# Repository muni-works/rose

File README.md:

# rose

rose is Muni's humanoid robot line: three sizes (mini, full, mega) meant to share
one structure and one electronics stack. The name is the past tense of *rise*.

**State today: design stage.** This repository is CAD sources, sizing and checking
scripts, fabrication packages, PCB designs and renders. It records no built robot:
the fab packages say nothing has been ordered or cut
([`body/fab/README.md`](body/fab/README.md), [`arm/V10.8.md`](arm/V10.8.md)),
and every image here is a render
([`head/renders/release/README.md`](head/renders/release/README.md)).
Numbers are model outputs or vendor figures, not measurements, unless a file says
otherwise. Muni's overall plan, and where rose sits in it, is at
<https://muni.works/research>.

| | |
|---|---|
|  |  |
| rose mini with the cortex head (render) | rose full, same design language (render) |

## Layout

| path | what it is |
|---|---|
| [`body/`](body) | The humanoid: mini (100 cm, 22 DoF, router-cut 3.2 mm plate, printed skins) and full, generated from one set of Python sources. Its fab package is in [`body/fab/`](body/fab). |
| [`head/`](head) | cortex, the head: a detachable module with the compute, battery, cameras, mics and a screen face, which docks on the neck or sits on a desk. Spec in [`SPEC.md`](head/SPEC.md); the "node" redesign, locked at v1.21 for a first print, in [`NODE-BRIEF.md`](head/NODE-BRIEF.md). |
| [`arm/`](arm) | lymb, a RobStride table arm that is also rose's arm. Current revision v10.8 ([`V10.8.md`](arm/V10.8.md)); v9 is kept bit-identical with a complete fab package. |
| [`electronics/`](electronics) | The boards: [`brain/`](electronics/brain) (RK3588S2 + STM32H7 compute), [`limb-controller/`](electronics/limb-controller) (one per limb), and [`brand/`](electronics/brand) (logo footprints for board art). |
| [`sizing/`](sizing) | The size ladder ([`family.py`](sizing/family.py)) and the mega actuator sizing ([`MEGA-SIZING.md`](sizing/MEGA-SIZING.md)). |

Each folder has a README with its run commands. Earlier design passes (the first
950 mm mini, the MyActuator full at 1800 mm, the rose-1 mega study, the quadruped
leg the body grew out of, the first box arm, the head mockups) were removed in
November 2026. They are in history at the tag
[`pre-restructure`](https://github.com/muni-works/rose/tree/pre-restructure).

## Tools

Sources are Python generators and [loon](https://vcad.io) files.

- **Python 3** for every sizing and checking script. `body/` also needs
  `numpy trimesh manifold3d shapely ezdxf scikit-image` (plus `rectpack` for
  `fab/make.py`).
- **[vcad](https://github.com/muni-works/vcad)** to evaluate and render `.loon`
  (`vcad`, `vcad-render`).
- **KiCad** (`kicad-cli`) for the board flows.

A few scripts read sibling checkouts under `~/Developer` (for example the Booster
K1 reference meshes in `body/k1.py`). `*.step` files are in Git LFS.

```bash
python3 sizing/family.py                       # the size ladder

cd body
python3 fab/make.py                            # plates (DXF), shells (STL), glass
python3 rom_mini.py                            # range of motion
python3 harness_check.py                       # cable clearance
python3 vcad_export.py                         # -> vcad/mini, vcad/full
cd ../head && sh export.sh                     # cortex.loon -> STEP / STL

python3 arm/rose_fork.py --summary             # from the repo root
python3 arm/fork_checks.py                     # mass, torque, stiffness
python3 arm/audit.py                           # interference, pinch points, ranges

./electronics/limb-controller/build.sh         # loon -> KiCad schematic, netcheck, ERC, PDF
./electronics/brain/build.sh
```

## The line, as sized by family.py

Each height is anchored to something real and rounded to the nearest 50 mm.

| | height | mass | actuators | compute | anchor |
|---|---:|---:|---|---|---|
| **rose mini** | 1200 mm | 18.0 kg | X6-60 / X4-36 / X4-10 | Orin NX | Booster K1 class (K1 is 1150) |
| **rose full** | 1750 mm | 55.5 kg *(est)* | X12 / X8 / X4-36 | Orin NX | a standard adult human |
| **rose mega** | 2000 mm | 64.3 kg | rana-190 / -140 / -100 | Jetson AGX Thor | a lumberjack: taller *and* broader |

mega carries a ×1.15 bulk factor on top of the height scale, so it is broad
rather than merely tall: 305 mm stance against full's 232 mm.

The intended design language across all three is bent 3 mm 5052 sheet for the
primary structure (laser blanks, press brake, bolts), 22 DOF: 6 per leg, 4 per
arm, 2 in the neck. Proportions scale from rose full's first 1130 mm layout.

| | single-leg 90° squat (from `family.py`) |
|---|---|
| mini | 33 N·m needed at the knee, 60 available |
| full | 149 N·m needed, 320 available |
| mega | 197 N·m needed, 262 available; holds to 140° of knee bend |

Single leg is the case that matters. Two-legged standing halves the load, but
walking spends most of its time on one foot and every landing lands on one.

This ladder (1200 / 1750 / 2000 mm, 22 DOF everywhere) is the August sizing
decision. The current body does not match it everywhere: its mini is 100 cm, and
the latest mega sizing ([`MEGA-SIZING.md`](sizing/MEGA-SIZING.md)) is 1.95 m.

### Actuator envelopes

When this table was sized, only four actuators had verified envelopes: X6-60,
X4-36, X4-10 (vendor STEP + the X-series V4 manual) and rana-100 rev D
(⌀100 × 44). For the larger ones `family.py` has torque but no dimensions, so
its packing check fails closed instead of inventing housings, and full's mass is
an estimate scaled from X6-60 by torque. [`rose_full_layout.py`](sizing/rose_full_layout.py)
has since taken X8 to X15 envelopes from vendor drawings for an 1800 mm layout;
`family.py` has not been updated to use them. rana-140 and rana-190 have no housing drawings
in this repo.

## What we learned sizing mega to jump

Unitree announced **Superman** on 17 Aug 2026: a claimed 2.0 m standing jump and
12.66 m/s top speed on 0.85 m legs and 360 N·m joints. Company demo, no independent
verification. Still, it is the number to design against, so [`family.py`](sizing/family.py)
puts vendor limits against it rather than picking a target by feel.

**rose mega is speed-limited, not torque-limited.** rana-190 has torque to spare
(the energy bound permits 0.65 m) but its 9.9 rad/s no-load output speed caps the
jump at **0.49 m**.

The reason is electrical, not mechanical. At peak current,

```
P = (Kt · I) · (V − I·R)/Kt = I · (V − I·R)
```

**Kt cancels.** Every actuator in the rana family delivers the same 1.3 kW peak
mechanical power, because peak power is set by the bus and the current limit alone
(48 V × 30 A), and gearing only trades torque against speed inside that envelope:

| | Kt | output torque | no-load speed | peak mech |
|---|---:|---:|---:|---:|
| rana-100 | 0.1657 | 36 N·m | 36.2 rad/s | 1.30 kW |
| rana-140 | 0.3326 | 96 N·m | 18.0 rad/s | 1.30 kW |
| rana-190 | 0.6055 | 262 N·m | 9.9 rad/s | 1.30 kW |

The ladder from rana-100 to rana-190 is a *torque* ladder, not a *power* ladder.
So jump height on this machine is an electrical spec:

| target | takeoff | knee rate | knee torque | both knees | vs available |
|---:|---:|---:|---:|---:|---:|
| 0.3 m | 2.43 m/s | 7.8 rad/s | 213 N·m | 3.3 kW | 1.3× |
| 0.5 m | 3.13 m/s | 10.0 rad/s | 289 N·m | 5.8 kW | 2.2× |
| 1.0 m | 4.43 m/s | 14.2 rad/s | 479 N·m | 13.6 kW | 5.2× |
| 2.0 m | 6.26 m/s | 20.0 rad/s | 860 N·m | 34.4 kW | 13.2× |

The levers are bus voltage and current, or series elastics that let the motors
work slowly and release fast. A bigger rana is not one of them.

## Limits

- **Nothing here has been validated on hardware.** Masses are budgets, torques
  are quasi-static, thermal figures come from lumped models. Several interface
  dimensions are marked ASSUMED in their files (RS06 bolt patterns in
  `body/quad.py`, parts of the cortex stack in
  [`head/CORTEX.md`](head/CORTEX.md)); the bench measurements still to take are
  listed in [`head/MEASURE.md`](head/MEASURE.md).
- **The rana actuators that mega depends on are not built**
  ([`sizing/MEGA-SIZING.md`](sizing/MEGA-SIZING.md)). The rana figures above are
  design values.
- **The jump model** is planar, knee-dominated and first-order: vendor limits in,
  a number out, no controller search. It ignores the hip and ankle contributions
  that would raise it and the transmission losses that would lower it. Both bounds
  it reports are ceilings.
- **The static check is one pass, not a fixed point.** A heavier actuator makes
  the robot heavier, which raises the torque it has to hold. Treat a marginal
  pass as marginal.
- **The packing check** (`family.py --pack`) compares actuator body against
  actuator body only (plates, fasteners and harness are not in it), and does not
  currently run: the layout it calls into changed when full was re-laid at 1800 mm.
- **The fab packages are not final.** The mini's printed skins are generated,
  not designed, and its BOM is partly unpriced
  ([`STATUS.md`](body/fab/mini/STATUS.md)); the arm's order lists are parked
  pending design approval.
- **Reference robots.** Comparison renders of the Unitree G1 / H2 and Booster K1
  are made from those vendors' published URDFs and meshes (`body/k1.py`).

## Used elsewhere

The vcad paper [*Exact Gradients Through a BRep Kernel*](https://muni.works/research/vcad)
and the [irys](https://github.com/muni-works/irys) renderer share a benchmark
built on one part from this repo: rose full's left shoulder-pitch output plate,
`L_shoA_shop_out` in
[`full/cad/links/shoA.loon` at commit `832192f`](https://github.com/muni-works/rose/blob/832192f32a1634ea856e0a8ded40eacd84e9d9e7/full/cad/links/shoA.loon).
irys's `rose_brep` example reads it at that commit. The file is no longer on
`main`, so check out that commit to reproduce the benchmark.

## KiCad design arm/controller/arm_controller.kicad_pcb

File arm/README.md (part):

# rose arm — fork concept

The design the box / bone iterations in `arm/` led to. Same RobStride actuators,
same flat-sheet-on-the-4040 manufacturing, a different kinematic idea.

```bash
python3 arm/rose_fork.py --summary                 # quick numbers
python3 arm/fork_checks.py                         # mass, torque, stiffness
python3 arm/audit.py                               # interference, pinch points, joint ranges
python3 arm/dfm.py                                 # process, bed fit, webs, unique parts
python3 arm/fab.py                                 # fab package: DXFs, nests, BOM, sleeves -> fab/
python3 arm/rose_fork.py '{"J2_sho_pitch": -55}' > pose.loon   # posed world geometry for vcad-render
```

## The idea

**Every pitch joint is a fork.** The parent holds the motor's stator ring
between its two side plates. The child straddles the parent: one plate bolts to
the output flange, the other rides a plain bearing on a hollow sleeve on the
joint axis. Parent and child share one centreline, so there are no offsets, no
zig-zag and no twist lever from an offset elbow.

**Links taper wide to narrow.** A link is wide at the joint behind it, where it
straddles, and narrow at the joint ahead, where it holds the next motor. That is
a constraint of the nesting that turned out to be the look.

**Cables never loop outside.**

- Pitch joints: the harness passes through the hollow sleeve on the axis. It only
  twists, so there is nothing to pinch or snag.
- Roll joints (forearm, tool) and base yaw: a clock-spring cassette in a collar
  coaxial with the joint. Collar halves are fixed / turning; the seam is the only
  moving interface and the cable is inside it.
- Inside links: in the inner slot of the bottom 2020 bars.

**Structure.** Two windowed 3 mm side plates, two 2020 bars along the bottom
corners, recessed 1.5 mm covers top and bottom. That closes the section for
torsion while the side plates are what you see.

## mini (2026-10-16): K1-scale, same three motor models

`ROSE_ARM=mini` in front of any script above builds the mini arm.

| joint | full | mini |
|---|---|---|
| J1 base yaw | RS04 | RS02 |
| J2 shoulder | RS04 | RS04 |
| J4 elbow | RS04 | RS02 |
| J5 forearm roll | RS02 | — (5 DOF) |
| J6 wrist pitch | RS02 | RS00 |
| J7 tool roll | RS00 | RS00 |

| | full | mini |
|---|---:|---:|
| upper / fore | 260 / 220 mm | 150 / 110 mm |
| jaw tips from the shoulder | 731 mm | 476 mm |
| mass | 8.3 kg | 4.8 kg |
| holds straight out, continuously | 1.44 kg | **0.72 kg** (elbow binds; shoulder 4.24) |
| sag / twist | 0.13 / 0.10 mm | 0.05 / 0.04 mm |
| interference, 209 poses / DFM web violations | none / none | none / none |

Why this selection, from the sweeps (`ROSE_ARM_MOTORS`, `ROSE_ARM_LEN`, `ROSE_ARM_TWIN_SH`,
`ROSE_ARM_NO_J5` override it):

- **An RS02 shoulder can't hold the arm at any length.** Even 100 / 90 mm holds only 0.16 kg: the
  wrist, gripper and base are about 2.2 kg whatever the link lengths. Every joint has one motor, so
  the shoulder is an RS04. Its mass sits on the axis, so it costs almost no torque.
- **The elbow sets the payload.** An RS06 shoulder would hold about the same 0.7 kg, but it would add a
  fourth motor model.
- **No forearm roll.** J5 sat inside the elbow lobe at these lengths. Dropping it is what lets the
  forearm come down to 110 mm.

What changed in the model to get there:

- **Flat, parallel upper-arm plates with a shorter elbow motor.** The RS02 elbow backs onto plate B
  at the shoulder's spacing. The forearm reaches its output through a 13.9 mm turned spacer instead
  of the 3 mm disc.
- **Holes sized per motor.** The plate-B centre hole and the nose bores follow each end's motor. The
  turret's slots and windows scale with the yaw disc. The foot is Ø170 mm with bolts on Ø140.
- **Higher shoulder.** The shoulder axis is at 150 mm, so the upper arm clears the base at +40°.

Open, beyond the full arm's list: the RS02 base yaw carries the whole tipping moment through a smaller
output bearing than the RS04's (check it against the manual). The checks still count RS04 sleeve
masses. The fab package (`fab.py`) has not been run for mini.

## v9 (2026-10-13): complete - every part ready to cut

**Stock: 1/8" (3.175 mm) 5052 for every plate, 1/4" for the foot** - what SendCutSend and local
suppliers carry. Nests are for 15 x 15 in sheets: three of 1/8" (one 24 x 48 in sheet cuts into
three with a strip left over) and one 12 x 12 in of 1/4". Re-run with `SHEET_MM=390` for bed size.

**Fab package in `fab/`**, generated from the model by `fab.py`:

- `parts/`: one DXF per unique router part (20), with outline, bolt patterns, bores, windows and slots
- `nest/`: one arm's parts on the 390 mm bed, three 3 mm sheets and one 6 mm. The 392 mm
  upper-arm plates go on at 21°.
- `BOM.md`: motors, stock, purchased parts, and 88 screws listed by interface. Each screw length is
  checked against the motor's thread depth.
- `SLEEVES.md` and `sleeve_*.svg`: the two turned sleeves, RS04 (3 off with the rig) and RS02

What changed to get there:

- **Real interfaces.** RS04, RS02 and RS00 come from their manual drawings (INTERFACES.md). Every
  motor is **mounted by its back face**. Plate A is a clearance plate round the nose, and the
  straddler bolts to the output through a 3 mm spacer disc. Every gap in the stack is 4 mm.
- **Every plate is flat and parallel.** v8's forearm flared 7° to reach round the J5 motor, so its
  plate could not sit flat on the elbow spacer. Now both roll motors are **cartridges**: the
  forearm and the wrist end in a cross plate, and the RS02 or RS00 back-mounts on its far face.
- **Tabs and slots** locate the covers, both end plates, the yoke bridge and the turret towers.
  The side plates' flat ends tab through the end plates.
- **One 3 mm stock** for every plate, covers included (6 mm foot only). Hub caps are closed cups.
- **Stiffness sees the lobe bores.** At each upper-arm lobe only the ring round the Ø102 / Ø90
  bores bends: 0.03 → 0.13 mm sag, still inside the 0.5 mm budget.
- **Sleeves are in the mass**, at 70 g each (RS04) and 22 g (RS02).

| | v8 | v9 |
|---|---:|---:|
| mass | 8.23 kg | 8.21 kg |
| moving mass | 5.59 kg | 5.64 kg |
| jaw tips from the shoulder | 693 mm | 731 mm |
| holds straight out, continuously | 1.49 kg | **1.49 kg** (wrist and shoulder bind together) |
| sag / twist | 0.03 / 0.10 mm | 0.13 / 0.11 mm |
| elbow / wrist range | ±110° / ±125° | −120…115° / ±135° |
| interference, 209 poses | none | none |
| DFM web violations | — | none (upper plates nest diagonally) |

Open:

- RS02 back-face and output thread depths are assumed at 6 mm, so measure before ordering screws.
- The yoke bridge turns about 1 mm in front of the stationary RS02 nose face. That is a safe pinch
  gap, but the flange proud height needs checking on a real motor.
- The crush points from `audit.py` still need a policy: soft limits, or force limiting.
- The cable loops under the two roll cartridges are drawn, but the clock-spring turns for roll
  are not designed yet.

## v8 (2026-10-13): DFM and efficiency pass

`dfm.py` classifies every part by process and checks router rules (bed fit,
webs >= 1.5 t and >= 4 mm, tool access); `audit.py` checks interference.

| | v7 (hybrid wrist) | v8 |
|---|---:|---:|
| mass | 9.54 kg | **8.23 kg** |
| moving mass | 6.49 kg | 5.59 kg |
| holds straight out, continuously | 1.13 kg | **1.49 kg** (shoulder binds; wrist 1.66) |
| plate stock | 1.5 / 3 / 4 / 6 mm | 3 mm (+ 1.5 mm upper covers, 6 mm foot) |
| unique router parts | 18 | 13 |
| turned parts | 6 | 1 (the steel sleeve, hidden) |

What moved the numbers: holder plates get a hole inside the motor's bolt circle
(that face only covers the motor); span-fitted windows; hub caps as thin cups
(117 g → 5 g each - they had been modelled as solid steel); a flat 3 mm yoke
bridge instead of an 8 mm disc (177 g → 24 g); B plates 4 → 3 mm with a 4 mm
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
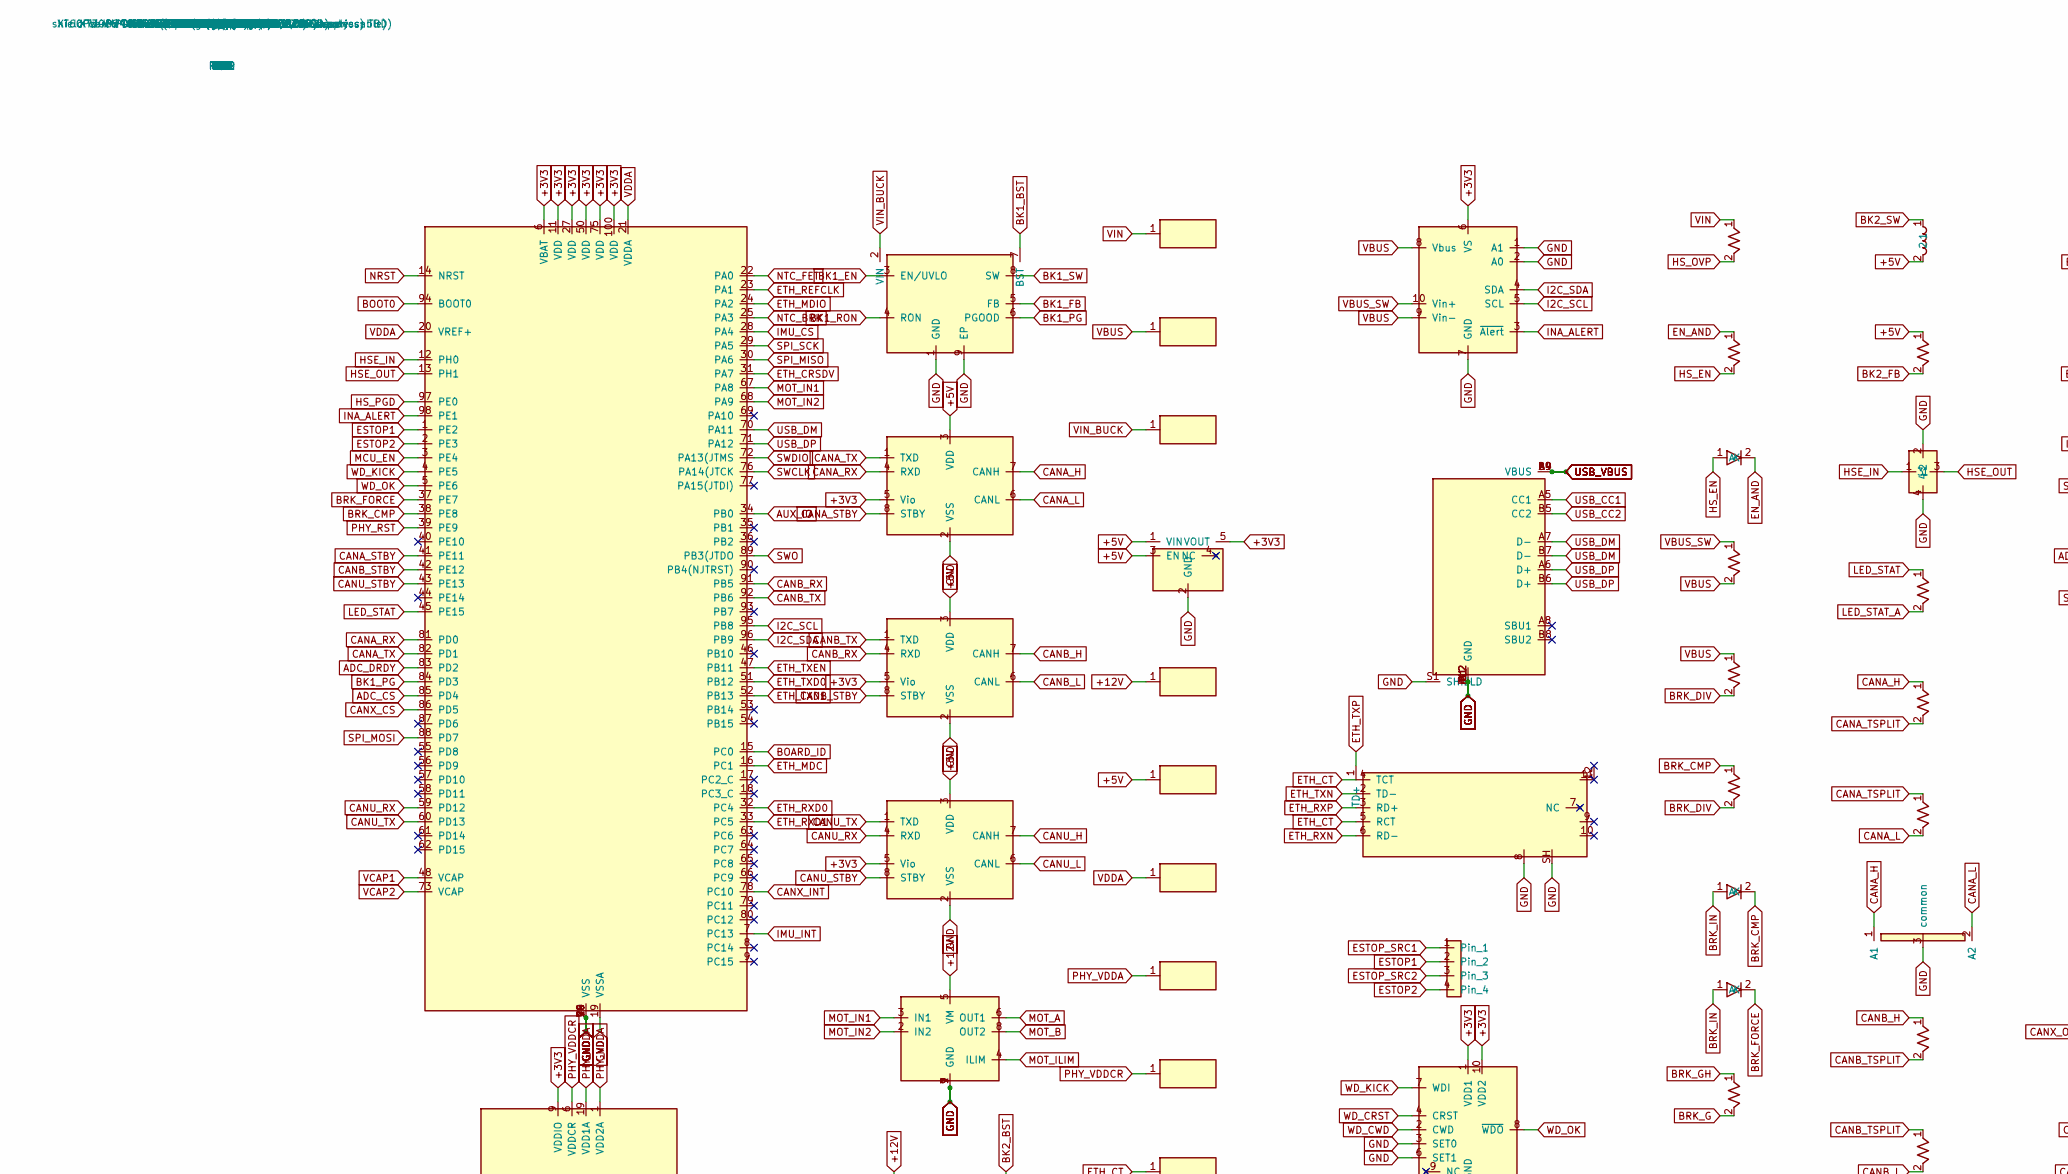
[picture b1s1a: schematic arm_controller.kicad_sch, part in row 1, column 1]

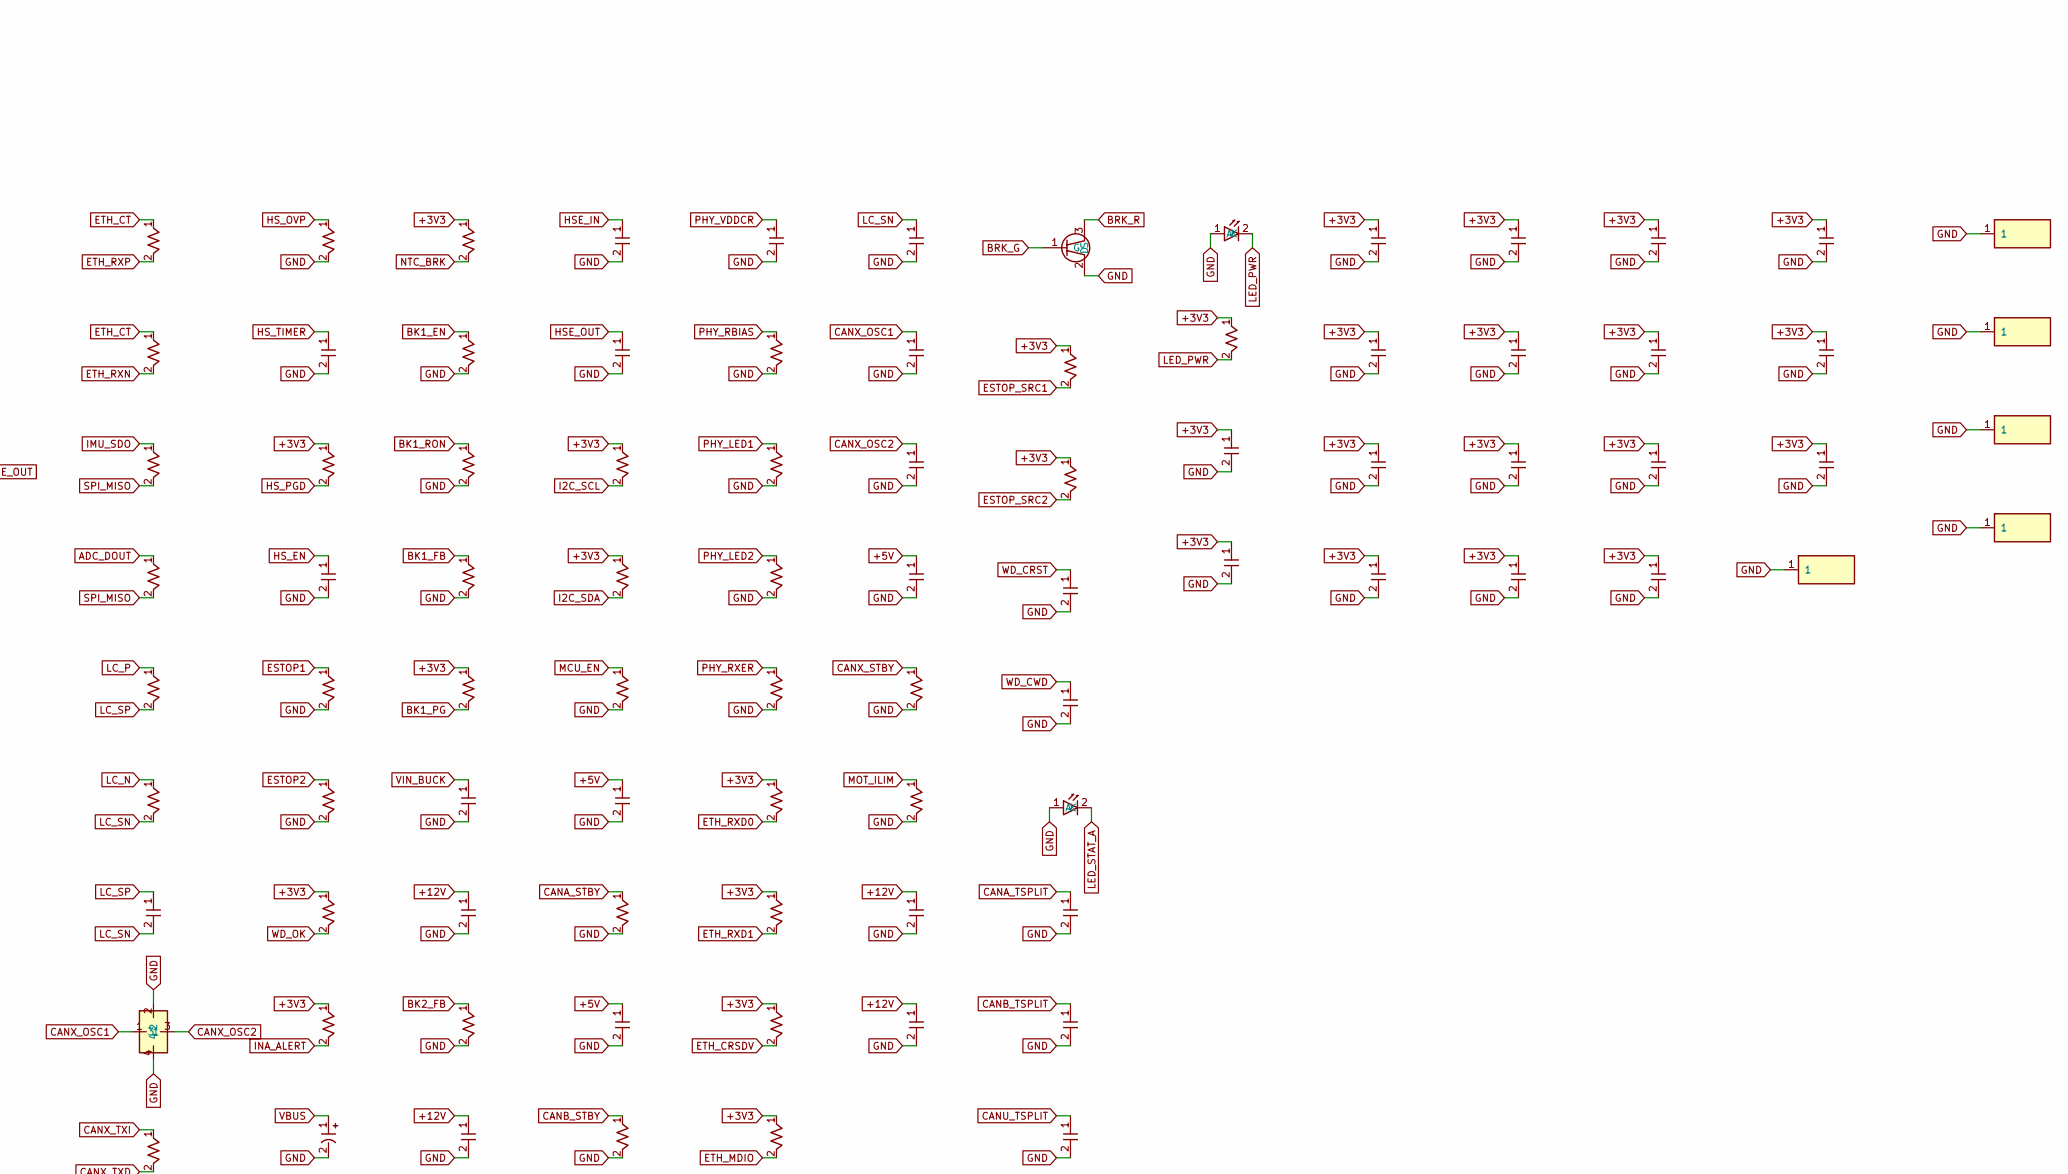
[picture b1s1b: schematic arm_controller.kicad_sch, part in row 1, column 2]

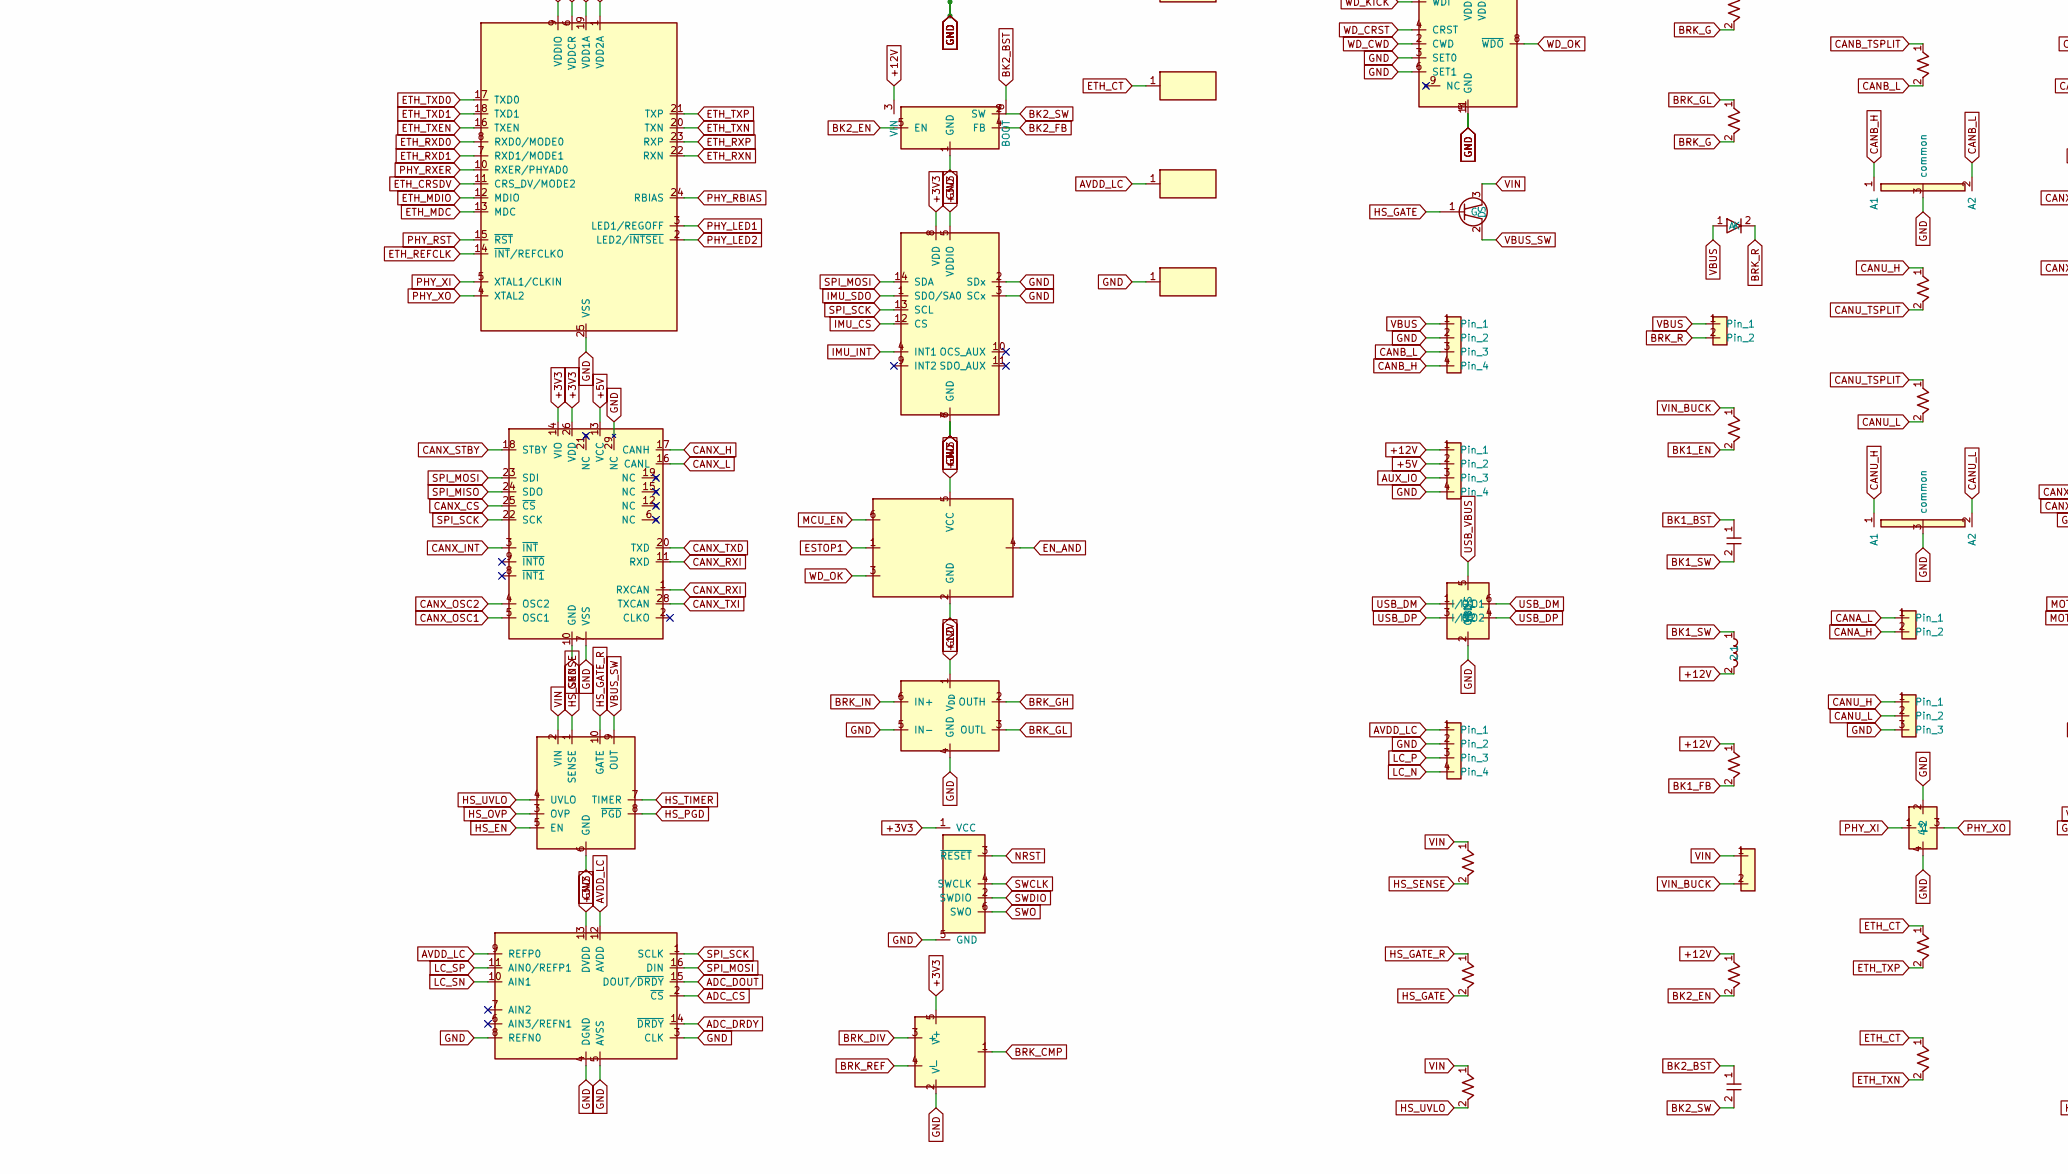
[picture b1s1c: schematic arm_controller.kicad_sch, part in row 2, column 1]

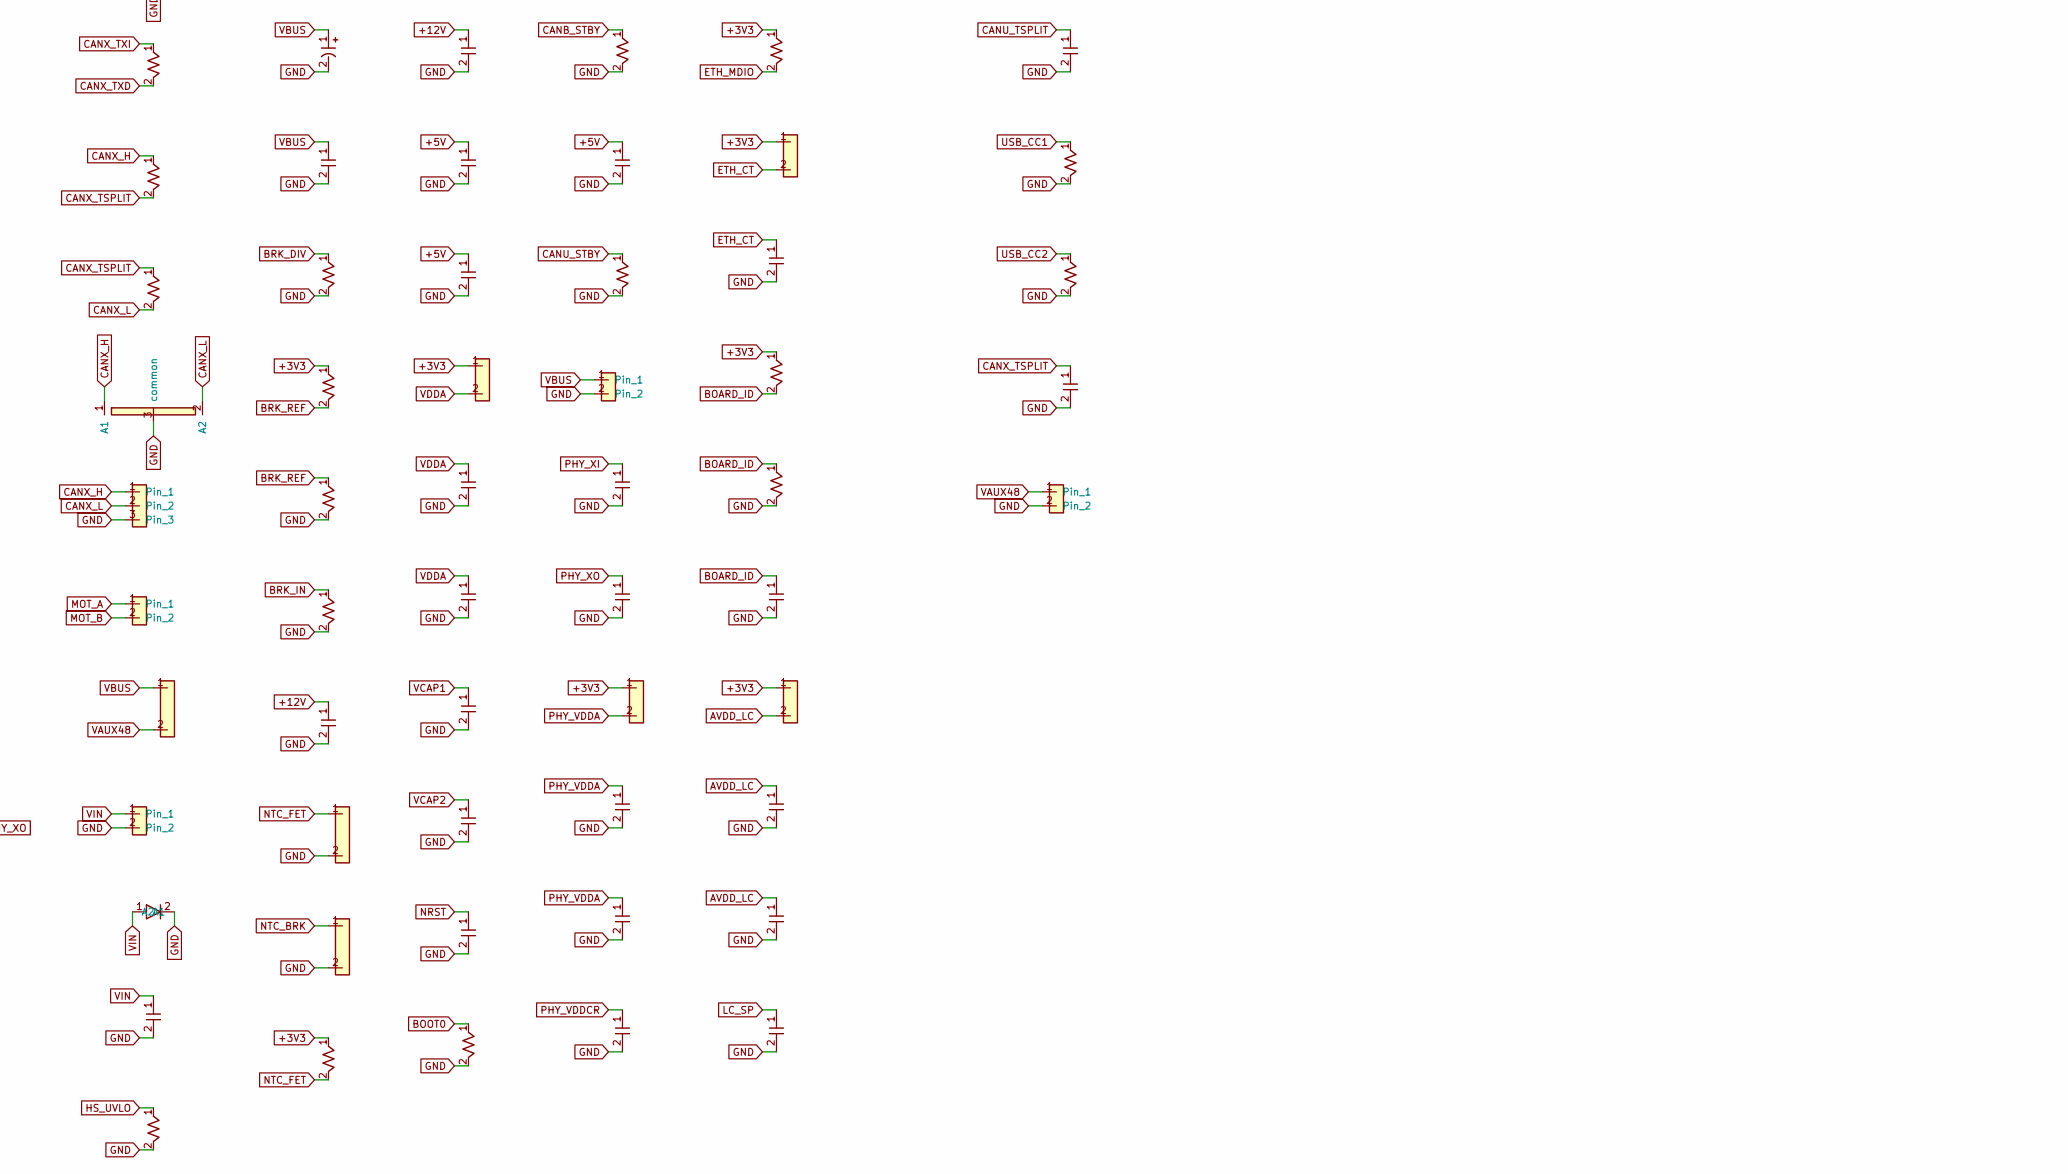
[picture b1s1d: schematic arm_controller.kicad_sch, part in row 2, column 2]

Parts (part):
C1, C8, C11: 2.2u 100V; C_1210_3225Metric
C2, C6, C13, C18, C19, C20, C21, C22, C25, C28, C31, C32, C33, C34, C35, C36, C43, C46, C47, C48, C49, C50, C52, C53, C59, C60, C61, C64: 100n; C_0402_1005Metric
C3: 390n; C_0402_1005Metric
C4, C5, C54: 10n; C_0402_1005Metric
C7: 220u 100V; CP_Radial_D12.5mm_P5.00mm
C9, C16, C24, C42, C44, C51: 1u; C_0402_1005Metric
C10: 2.2n; C_0402_1005Metric
C12: 22u 25V; C_0805_2012Metric
C14: 10u 25V; C_0805_2012Metric
C15: 22u; C_0805_2012Metric
C17: 10u; C_0805_2012Metric
C23: 4.7u; C_0805_2012Metric
C26, C27: 2.2u; C_0402_1005Metric
C29, C30, C40, C41: 10p; C_0402_1005Metric
C37, C38, C39, C62: 4.7n; C_0402_1005Metric
C45: 470p; C_0402_1005Metric
C55, C56: 1n; C_0402_1005Metric
C57, C58: 12p; C_0402_1005Metric
C63: 10u 25V; C_1210_3225Metric
D1: SMDJ60A; D_SMC
D2, D3, D10: BAT54; D_SOD-123
D4: STPS10H100 100V; D_SMC
D5: green 3V3; LED_0603_1608Metric
D6: blue status; LED_0603_1608Metric
D7, D8, D9, D11: PESD2CAN; SOT-23
F1: PTC 60V 1.1A hold (Bel 0ZCF0110AF2A); Fuse_2920_7451Metric
FB1, FB2, FB3, FB5: 600R@100MHz; L_0603_1608Metric
FB4: BLM31KN601SN1 (1206, 100 V); L_1206_3216Metric
H1, H2, H3, H4: M3; MountingHole_3.2mm_M3_Pad_Via
J1: XT60PW-M 48V in (fuse: ATM 50A inline in the supp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; AMASS_XT60PW-M_1x02_P7.20mm_Horizontal
J2: E-stop, 2-ch NC; JST_GH_SM04B-GHS-TB_1x04-1MP_P1.25mm_Horizontal
J3: XT30PW-M brake resistor 3R3 200W; AMASS_XT30PW-M_1x02_P2.50mm_Horizontal
J4: TC2030 SWD; Tag-Connect_TC2030-IDC-NL_2x03_P1.27mm_Vertical
J5: XT30PW-M RS04 power (3-way split in the harness); AMASS_XT30PW-M_1x02_P2.50mm_Horizontal
J8: GH1.25 RS04 CAN; JST_GH_SM02B-GHS-TB_1x02-1MP_P1.25mm_Horizontal
J9: XT30PB(2+2)-M wrist bus; AMASS_XT30PB_2+2_M
J10: GH CAN-FD uplink; JST_GH_SM03B-GHS-TB_1x03-1MP_P1.25mm_Horizontal
J11: GH aux 12V/5V/IO; JST_GH_SM04B-GHS-TB_1x04-1MP_P1.25mm_Horizontal
J12: USB-C; USB_C_Receptacle_GCT_USB4105-xx-A_16P_TopMnt_Horizontal
J13: HR911105A; RJ45_Hanrun_HR911105A_Horizontal
J14: GH load cell EXC+/EXC-/S+/S-; JST_GH_SM04B-GHS-TB_1x04-1MP_P1.25mm_Horizontal
J15: GH CAN-FD X (second limb / tool); JST_GH_SM03B-GHS-TB_1x03-1MP_P1.25mm_Horizontal
J16: GH brushed motor; JST_GH_SM02B-GHS-TB_1x02-1MP_P1.25mm_Horizontal
J17: XT30PW-M 48 V aux out; AMASS_XT30PW-M_1x02_P2.50mm_Horizontal
L1: 22u 1.5A; L_Bourns_SRN6045TA
L2: 4.7u 3A; L_Bourns_SRN6045TA
PF1, PF2, PF3, PF4, PF5, PF6, PF8, PF9, PF10, PF11, PF12: PWR_FLAG
Q1, Q2: IPT015N10N5 100V 1.5mR; Infineon_PG-HSOF-8-1
R1: 20k; R_0402_1005Metric
R2: 10; R_0402_1005Metric
R3: 220k; R_0603_1608Metric
R4, R6, R7, R10, R12, R13, R15, R18, R19, R24, R25, R27, R36, R41, R45, R49, R56, R57, R58, R59, R60, R61, R67, R71: 10k; R_0402_1005Metric
R5: 330k; R_0603_1608Metric
R8: 1M; R_0402_1005Metric
R9, R11, R35, R40, R69, R70: 1k; R_0402_1005Metric
R14: 0.5m 4-term; R_2512_6332Metric
R16: 301k; R_0603_1608Metric
R17: 9.09k; R_0402_1005Metric
R20: 665k; R_0402_1005Metric
R21, R26, R29, R31, R32, R33, R39: 100k; R_0402_1005Metric
R22: 4.7; R_0402_1005Metric
R23: 2.2; R_0402_1005Metric
R28: 150k; R_0402_1005Metric
R30: 11k; R_0402_1005Metric
R34: 13.3k; R_0402_1005Metric
R37, R38: 2.2k; R_0402_1005Metric
R42, R43, R46, R47, R50, R51, R72, R73: 60.4; R_0402_1005Metric
R53, R54: 5.1k; R_0402_1005Metric
R55: 12.1k 1%; R_0402_1005Metric
R62: 1.5k; R_0402_1005Metric
R63, R64, R65, R66: 49.9 1%; R_0402_1005Metric
R68: ID: DNP arm, 10k leg, 4.7k torso, 2.2k head; R_0402_1005Metric
R74: 82k; R_0402_1005Metric
R75, R76: 33; R_0402_1005Metric
R77: 0; R_0402_1005Metric
SH1: shield can 24x20x2 (frame + lid, e.g. Harwin S02 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; shield_mcu
TH1: 10k NTC (FETs); R_0402_1005Metric
TH2: 10k NTC (brake R); R_0402_1005Metric
U1: LM5060; VSSOP-10_3x3mm_P0.5mm
U2: 74LVC1G11; SOT-23-6
U3: TPS3430; Texas_DRC0010J_ThermalVias
U4: INA228; VSSOP-10_3x3mm_P0.5mm
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
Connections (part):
+3V3: C6.1, C17.1, C18.1, C19.1, C20.1, C21.1, C22.1, C23.1, C32.1, C34.1, C36.1, C46.1, C49.1, C50.1, C53.1, C59.1, C60.1, FB1.1, FB2.1, FB3.1, FB5.1, J4.1 (VCC), R7.1, R9.1, R11.1, R13.1, R15.1, R18.1, R24.1, R25.1, R31.1, R35.1, R37.1, R38.1, R59.1, R60.1, R61.1, R62.1, R67.1, U2.5 (VCC), U3.1 (VDD1), U3.10 (VDD2), U4.6 (VS), U5.5 (V+), U9.5 (VOUT), U10.6 (VBAT), U10.11 (VDD), U10.27 (VDD), U10.50 (VDD), U10.75 (VDD), U10.100 (VDD), U11.5 (Vio), U12.5 (Vio), U13.5 (Vio), U15.9 (VDDIO), U16.5 (VDDIO), U16.8 (VDD), U17.13 (DVDD), U18.14 (VIO), U18.26 (VDD)
+5V: C15.1, C16.1, C31.1, C33.1, C35.1, C61.1, J11.2, L2.2, PF5.1, R33.1, U9.1 (VIN), U9.3 (EN), U11.3 (VDD), U12.3 (VDD), U13.3 (VDD), U18.13 (VCC)
+12V: C9.1, C12.1, C14.1, C63.1, C64.1, J11.1, L1.2, PF4.1, R29.1, R32.1, U6.1 (V_{DD}), U8.3 (VIN), U19.5 (VM)
ADC_CS: U10.85 (PD4), U17.2 (~CS)
ADC_DOUT: R76.1, U17.15 (DOUT/~DRDY)
ADC_DRDY: U10.83 (PD2), U17.14 (~DRDY)
AUX_IO: J11.3, U10.34 (PB0)
AVDD_LC: C51.1, C52.1, FB5.2, J14.1, PF12.1, U17.9 (REFP0), U17.12 (AVDD)
BK1_BST: C10.1, U7.7 (BST)
BK1_EN: R26.2, R27.1, U7.3 (EN/UVLO)
BK1_FB: R29.2, R30.1, U7.5 (FB)
BK1_PG: R31.2, U7.6 (PGOOD), U10.84 (PD3)
BK1_RON: R28.1, U7.4 (RON)
BK1_SW: C10.2, L1.1, U7.8 (SW)
BK2_BST: C13.1, U8.6 (BOOT)
BK2_EN: R32.2, U8.5 (EN)
BK2_FB: R33.2, R34.1, U8.4 (FB)
BK2_SW: C13.2, L2.1, U8.2 (SW)
BOARD_ID: C48.1, R67.2, R68.1, U10.15 (PC0)
BOOT0: R36.1, U10.94 (BOOT0)
BRK_CMP: D2.2 (A), R20.1, U5.1, U10.38 (PE8)
BRK_DIV: R16.2, R17.1, R20.2, U5.3 (+)
BRK_FORCE: D3.2 (A), U10.37 (PE7)
BRK_G: Q2.1 (G), R22.2, R23.2
BRK_GH: R22.1, U6.2 (OUTH)
BRK_GL: R23.1, U6.3 (OUTL)
BRK_IN: D2.1 (K), D3.1 (K), R21.1, U6.6 (IN+)
BRK_R: D4.2 (A), J3.2, Q2.3 (D)
BRK_REF: R18.2, R19.1, U5.4 (-)
CANA_H: D7.1 (A1), J8.2, R42.1, U11.7 (CANH)
CANA_L: D7.2 (A2), J8.1, R43.2, U11.6 (CANL)
CANA_RX: U10.81 (PD0), U11.4 (RXD)
CANA_STBY: R41.1, U10.41 (PE11), U11.8 (STBY)
CANA_TSPLIT: C37.1, R42.2, R43.1
CANA_TX: U10.82 (PD1), U11.1 (TXD)
CANB_H: D8.1 (A1), J9.4, R46.1, U12.7 (CANH)
CANB_L: D8.2 (A2), J9.3, R47.2, U12.6 (CANL)
CANB_RX: U10.91 (PB5), U12.4 (RXD)
CANB_STBY: R45.1, U10.42 (PE12), U12.8 (STBY)
CANB_TSPLIT: C38.1, R46.2, R47.1
CANB_TX: U10.92 (PB6), U12.1 (TXD)
CANU_H: D9.1 (A1), J10.1, R50.1, U13.7 (CANH)
CANU_L: D9.2 (A2), J10.2, R51.2, U13.6 (CANL)
CANU_RX: U10.59 (PD12), U13.4 (RXD)
CANU_STBY: R49.1, U10.43 (PE13), U13.8 (STBY)
CANU_TSPLIT: C39.1, R50.2, R51.1
CANU_TX: U10.60 (PD13), U13.1 (TXD)
CANX_CS: U10.86 (PD5), U18.25 (~CS)
CANX_H: D11.1 (A1), J15.1, R72.1, U18.17 (CANH)
CANX_INT: U10.78 (PC10), U18.3 (~INT)
CANX_L: D11.2 (A2), J15.2, R73.2, U18.16 (CANL)
CANX_OSC1: C57.1, U18.5 (OSC1), Y3.1
CANX_OSC2: C58.1, U18.4 (OSC2), Y3.3
CANX_RXI: U18.1 (RXCAN), U18.11 (RXD)
CANX_STBY: R71.1, U18.18 (STBY)
CANX_TSPLIT: C62.1, R72.2, R73.1
CANX_TXD: R77.2, U18.20 (TXD)
CANX_TXI: R77.1, U18.28 (TXCAN)
EN_AND: D10.2 (A), R8.1, U2.4
ESTOP1: J2.2, R10.1, U2.1, U10.1 (PE2)
ESTOP2: J2.4, R12.1, U10.2 (PE3)
ESTOP_SRC1: J2.1, R9.2
ESTOP_SRC2: J2.3, R11.2
ETH_CRSDV: R61.2, U10.31 (PA7), U15.11 (CRS_DV/MODE2)
ETH_CT: C47.1, FB3.2, J13.4 (TCT), J13.5 (RCT), PF10.1, R63.1, R64.1, R65.1, R66.1
ETH_MDC: U10.16 (PC1), U15.13 (MDC)
ETH_MDIO: R62.2, U10.24 (PA2), U15.12 (MDIO)
ETH_REFCLK: U10.23 (PA1), U15.14 (~INT/REFCLKO)
ETH_RXD0: R59.2, U10.32 (PC4), U15.8 (RXD0/MODE0)
ETH_RXD1: R60.2, U10.33 (PC5), U15.7 (RXD1/MODE1)
ETH_RXN: J13.6 (RD-), R66.2, U15.22 (RXN)
ETH_RXP: J13.3 (RD+), R65.2, U15.23 (RXP)
ETH_TXD0: U10.51 (PB12), U15.17 (TXD0)
ETH_TXD1: U10.52 (PB13), U15.18 (TXD1)
ETH_TXEN: U10.47 (PB11), U15.16 (TXEN)
ETH_TXN: J13.2 (TD-), R64.2, U15.20 (TXN)
ETH_TXP: J13.1 (TD+), R63.2, U15.21 (TXP)
GND: C1.2, C2.2, C3.2, C4.2, C5.2, C6.2, C7.2, C8.2, C9.2, C11.2, C12.2, C14.2, C15.2, C16.2, C17.2, C18.2, C19.2, C20.2, C21.2, C22.2, C23.2, C24.2, C25.2, C26.2, C27.2, C28.2, C29.2, C30.2, C31.2, C32.2, C33.2, C34.2, C35.2, C36.2, C37.2, C38.2, C39.2, C40.2, C41.2, C42.2, C43.2, C44.2, C45.2, C46.2, C47.2, C48.2, C49.2, C50.2, C51.2, C52.2, C53.2, C55.2, C56.2, C57.2, C58.2, C59.2, C60.2, C61.2, C62.2, C63.2, C64.2, D1.2 (A2), D5.1 (K), D6.1 (K), D7.3 (common), D8.3 (common), D9.3 (common), D11.3 (common), H1.1, H2.1, H3.1, H4.1, J1.2, J4.5 (GND), J5.2, J9.2, J10.3, J11.4, J12.A1 (GND), J12.A12 (GND)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
HSE_IN: C29.1, U10.12 (PH0), Y1.1
HSE_OUT: C30.1, U10.13 (PH1), Y1.3
HS_EN: C3.1, D10.1 (K), R8.2, U1.5 (EN)
HS_GATE: Q1.1 (G), R2.2
HS_GATE_R: R2.1, U1.10 (GATE)
HS_OVP: R5.2, R6.1, U1.3 (OVP)
HS_PGD: R7.2, U1.8 (~PGD), U10.97 (PE0)
HS_SENSE: R1.2, U1.1 (SENSE)
HS_TIMER: C2.1, U1.7 (TIMER)
HS_UVLO: R3.2, R4.1, U1.4 (UVLO)
I2C_SCL: R37.2, U4.5 (SCL), U10.95 (PB8)
I2C_SDA: R38.2, U4.4 (SDA), U10.96 (PB9)
IMU_CS: U10.28 (PA4), U16.12 (CS)
IMU_INT: U10.7 (PC13), U16.4 (INT1)
IMU_SDO: R75.1, U16.1 (SDO/SA0)
INA_ALERT: R15.2, U4.3 (~Alert), U10.98 (PE1)
LC_N: J14.4, R70.1
LC_P: J14.3, R69.1
LC_SN: C54.2, C56.1, R70.2, U17.10 (AIN1)
LC_SP: C54.1, C55.1, R69.2, U17.11 (AIN0/REFP1)
LED_PWR: D5.2 (A), R35.2
LED_STAT: R40.1, U10.45 (PE15)
LED_STAT_A: D6.2 (A), R40.2
MCU_EN: R39.1, U2.6, U10.3 (PE4)
MOT_A: J16.1, U19.6 (OUT1)
MOT_B: J16.2, U19.8 (OUT2)
MOT_ILIM: R74.1, U19.4 (ILIM)
MOT_IN1: U10.67 (PA8), U19.3 (IN1)
MOT_IN2: U10.68 (PA9), U19.2 (IN2)
NRST: C28.1, J4.3 (~RESET), U10.14 (NRST)
NTC_BRK: R25.2, TH2.1, U10.25 (PA3)
NTC_FET: R24.2, TH1.1, U10.22 (PA0)
PHY_LED1: R56.1, U15.3 (LED1/REGOFF)
PHY_LED2: R57.1, U15.2 (LED2/~INTSEL)
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
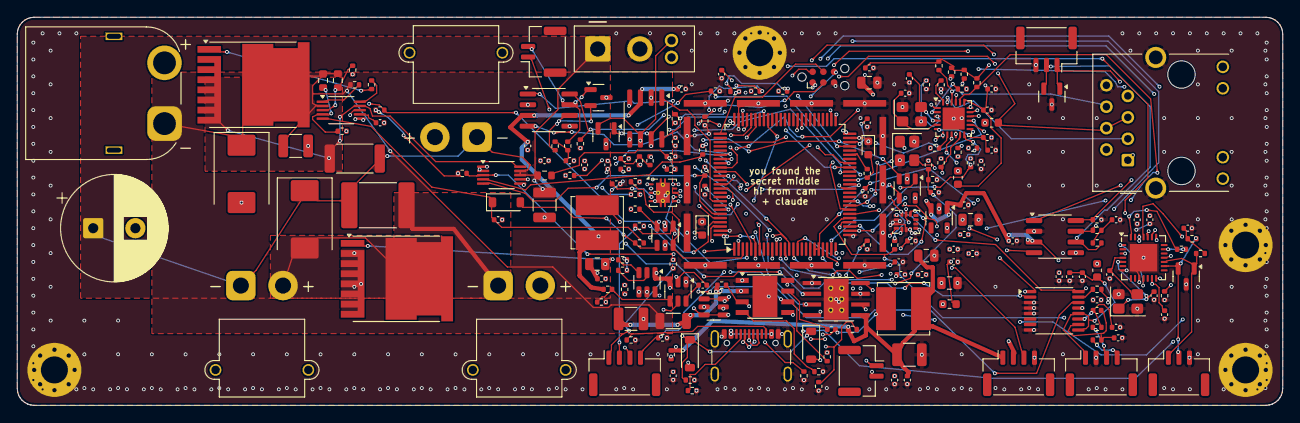
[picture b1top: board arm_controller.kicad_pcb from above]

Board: 6 copper layers, 150.0 x 46.0 mm, 220 parts (0 on the bottom side), 142 nets.

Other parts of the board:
ART1: rose_back
EGG1: rose_egg_mcu
LBB_J1: lblb_J1
LBB_J2: lblb_J2
LBB_J3: lblb_J3
LBB_J5: lblb_J5
LBB_J8: lblb_J8
LBB_J9: lblb_J9
LBB_J10: lblb_J10
LBB_J11: lblb_J11
LBB_J12: lblb_J12
LBB_J13: lblb_J13
LBB_J14: lblb_J14
LBB_J15: lblb_J15
LBB_J16: lblb_J16
LBB_J17: lblb_J17
RING1: edge_ring

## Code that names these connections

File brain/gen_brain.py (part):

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

def soc_ball(tok):
    """The one ball whose datasheet name has `tok` as a whole function ('GPIO1_B3', 'XIN_24M')."""
    m = [b for b, n in SOC if re.search(r'(^|/)\s*' + re.escape(tok) + r'(_[a-z])?(/|$)', n)]
    assert len(m) == 1, (tok, m)
    return m[0]
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for name, val, vsel, scl, sda in rk860:
    out_net = f'VDD_{"CPU_" if "BIG" in name else ""}{name}_S0'
    sw = f'{name}_LX'
    pins = {'A1': vsel, 'A2': 'BIG_NPU_EN', 'A3': scl, 'A4': out_net, 'B1': sda, 'B4': 'GND'}
    for b in ('B2', 'B3', 'C1', 'C2', 'C3', 'C4'):
        pins[b] = 'GND'
    for b in ('D1', 'D2', 'E1', 'E2'):
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soc('PMIC_SLEEP5', 'VSEL5')
soc('PMIC_SLEEP6', 'VSEL6')
soc('PMIC_INT_L', 'PMIC_INT_L')
soc('GPIO0_A5', 'PMIC_SPI_CLK_SOC')
soc('GPIO0_A6', 'PMIC_SPI_MOSI_SOC')
soc('GPIO0_B1', 'PMIC_SPI_CS')
r('22R', 'PMIC_SPI_CLK_SOC', 'PMIC_SPI_CLK')
r('22R', 'PMIC_SPI_MOSI_SOC', 'PMIC_SPI_MOSI')
soc('GPIO0_D1', 'I2C0_SCL')
soc('GPIO0_D2', 'I2C0_SDA')
soc('GPIO0_B7', 'I2C2_SCL')
soc('GPIO0_C0', 'I2C2_SDA')
soc('SARADC_IN0_BOOT', 'SARADC_IN0_BOOT')
r('100k', 'VCCA_1V8_S0', 'SARADC_IN0_BOOT')
c('1n', 'SARADC_IN0_BOOT')
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    decouple('VCC_3V3_S0', '1u')

emit(';; ---- SoC <-> H7: SPI0_M2 (SoC master, 1 kHz bus exchange), UART6_M1 (H7 bootloader + console), IRQ, reset, BOOT0')
soc('GPIO1_B1', 'RT_MISO')
soc('GPIO1_B2', 'RT_MOSI')
soc('GPIO1_B3', 'RT_SCK')
soc('GPIO1_B4', 'RT_CS_n')
soc('GPIO1_A0', 'RT_TX')      # UART6_RX_M1 <- H7 TX
soc('GPIO1_A1', 'RT_RX')      # UART6_TX_M1 -> H7 RX
soc('GPIO1_A4', 'RT_IRQ')
soc('GPIO1_A7', 'RT_NRST')
soc('GPIO1_D0' if any('GPIO1_D0' in n for _, n in SOC) else 'GPIO1_C0', 'RT_BOOT0')
soc('GPIO0_B5', 'SOC_UART2_TX')   # debug console to a header
soc('GPIO0_B6', 'SOC_UART2_RX')
part('J7', 'Connector_Generic:Conn_01x03', 'SoC console (UART2, 1.5 Mbaud)', 'Connector_JST:JST_GH_SM03B-GHS-TB_1x03-1MP_P1.25mm_Horizontal',
     [('1', 'SOC_UART2_TX'), ('2', 'SOC_UART2_RX'), ('3', 'GND')])

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        h7_net[num] = f'VCAP{i + 1}'
h7('NRST', 'RT_NRST')
h7('BOOT0', 'RT_BOOT0')
h7('PH0', 'HSE_IN')
h7('PH1', 'HSE_OUT')
# FDCAN1 PD0/PD1, FDCAN2 PB5/PB6, FDCAN3 PD12/PD13: the limb controller's pin-out
for k, (rx, tx) in enumerate((('PD0', 'PD1'), ('PB5', 'PB6'), ('PD12', 'PD13'))):
    h7(rx, f'CAN{k}_RX')
    h7(tx, f'CAN{k}_TX')
# SPI2 slave to the SoC: PB12 NSS, PB13 SCK, PB14 MISO, PB15 MOSI
h7('PB12', 'RT_CS_n')
h7('PB13', 'RT_SCK')
h7('PB14', 'RT_MISO')
h7('PB15', 'RT_MOSI')
h7('PA9', 'RT_TX')     # USART1: the H7's ROM bootloader port
h7('PA10', 'RT_RX')
h7('PE7', 'RT_IRQ')
# SPI1 to the three MCP251863s: PA5 SCK, PA6 MISO, PD7 MOSI; CS/INT per chip
h7('PA5', 'CANX_SCK')
h7('PA6', 'CANX_MISO')
h7('PD7', 'CANX_MOSI')
for k, (cs, it) in enumerate((('PD3', 'PD4'), ('PD5', 'PD6'), ('PC10', 'PC11'))):
    h7(cs, f'CANX{k}_CS')
    h7(it, f'CANX{k}_INT')
# SPI4 to the black-box flash: PE2 SCK, PE5 MISO, PE6 MOSI, PE4 CS
h7('PE2', 'BB_SCK')
h7('PE5', 'BB_MISO')
h7('PE6', 'BB_MOSI')
h7('PE4', 'BB_CS_n')
# the body clock: TIM1 CH1 = SYNC to every limb, CH2/CH3 = camera triggers
h7('PE9', 'SYNC_OUT')
h7('PE11', 'CAM0_TRIG_RT')
h7('PE13', 'CAM1_TRIG_RT')
h7('PA0', 'PFAIL_DIV')          # ADC/COMP input: 12 V divided
h7('PC0', 'ESTOP_OK_RT')
h7('PC1', 'PACK_OK_RT')
h7('PA13', 'SWDIO')
h7('PA14', 'SWCLK')
h7('PB3', 'SWO')
h7('PE0', 'LED_R')
h7('PE1', 'LED_G')
h7('PE3', 'LED_B')
h7('PD8', 'CAN0_STBY')
h7('PD9', 'CAN1_STBY')
h7('PD10', 'CAN2_STBY')
h7('PD11', 'CAN5_STBY')
h7('PD14', 'SOC_PWR_EN_RT')
part('U_RT', 'MCU_ST_STM32H7:STM32H723VGTx', 'STM32H723VGT6', 'Package_QFP:LQFP-100_14x14mm_P0.5mm', sorted(h7_net.items(), key=lambda kv: int(kv[0])))
decouple('3V3_RT', '8x100n', '4.7u')
fb('3V3_RT', 'VDDA_RT', '600R@100MHz')
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# ================================================================ CAN-FD buses and limb ports
emit()
emit(';; ---- six CAN-FD buses: 0-2 on the H7\'s FDCANs, 3-4 on MCP251863s, 5 (BMS) on the third MCP251863')
emit(';; limb port: GH 5-pin, CAN_H, CAN_L, SYNC, ESTOP_OK, GND (power comes from the spine on its own XT30)')
MCP = kicad_pins('Interface_CAN_LIN', 'MCP251863T-E-9PX')


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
